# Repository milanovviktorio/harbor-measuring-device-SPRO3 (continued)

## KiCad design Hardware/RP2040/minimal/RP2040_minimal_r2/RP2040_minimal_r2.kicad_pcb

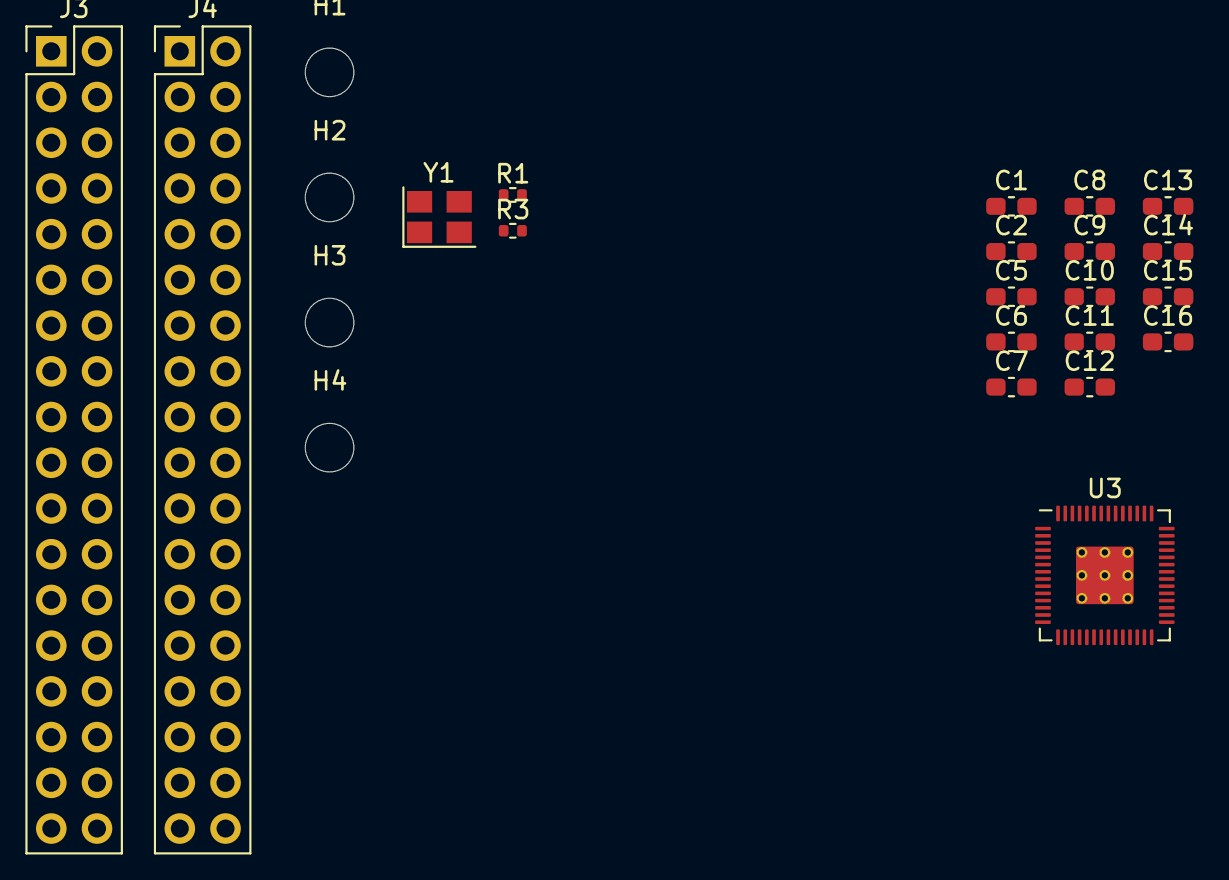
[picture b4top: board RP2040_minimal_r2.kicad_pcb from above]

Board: 2 copper layers, 24 parts (0 on the bottom side), 39 nets, no tracks yet.

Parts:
C1, C2: 27pF; C_0603_1608Metric_Pad1.08x0.95mm_HandSolder
C5, C6, C7, C9, C11, C12, C13, C14, C15, C16: 100n; C_0603_1608Metric_Pad1.08x0.95mm_HandSolder
C8, C10: 1u; C_0603_1608Metric_Pad1.08x0.95mm_HandSolder
H1, H2, H3, H4: MountingHole; MountingHole_2.7mm_M2.5
J3, J4: Conn_02x18_Odd_Even; PinHeader_2x18_P2.54mm_Vertical
R1: 1k; R_0402_1005Metric
R3: 10k; R_0402_1005Metric
U3: RP2040; RP2040-QFN-56
Y1: 12Mhz; Crystal_SMD_Abracon_ABM8G-4Pin_3.2x2.5mm

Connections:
+1V1: C6.1, C7.1, C8.1, U3.23 (DVDD), U3.45 (VREG_VOUT), U3.50 (DVDD)
+3V3: C5.1, C9.1, C10.1, C11.1, C12.1, C13.1, C14.1, C15.1, C16.1, J3.2, R3.1, U3.1 (IOVDD), U3.10 (IOVDD), U3.22 (IOVDD), U3.33 (IOVDD), U3.42 (IOVDD), U3.43 (ADC_AVDD), U3.44 (VREG_IN), U3.48 (USB_VDD), U3.49 (IOVDD)
/GPIO0: J3.4, U3.2 (GPIO0)
/GPIO1: J3.6, U3.3 (GPIO1)
/GPIO2: J3.8, U3.4 (GPIO2)
/GPIO3: J3.10, U3.5 (GPIO3)
/GPIO4: J3.12, U3.6 (GPIO4)
/GPIO5: J3.14, U3.7 (GPIO5)
/GPIO6: J3.16, U3.8 (GPIO6)
/GPIO7: J3.18, U3.9 (GPIO7)
/GPIO8: J3.20, U3.11 (GPIO8)
/GPIO9: J3.22, U3.12 (GPIO9)
/GPIO10: J3.24, U3.13 (GPIO10)
/GPIO11: J3.26, U3.14 (GPIO11)
/GPIO12: J3.28, U3.15 (GPIO12)
/GPIO13: J3.30, U3.16 (GPIO13)
/GPIO14: J3.32, U3.17 (GPIO14)
/GPIO15: J3.34, U3.18 (GPIO15)
/GPIO16: J4.27, U3.27 (GPIO16)
/GPIO17: J4.25, U3.28 (GPIO17)
/GPIO18: J4.23, U3.29 (GPIO18)
/GPIO19: J4.21, U3.30 (GPIO19)
/GPIO20: J4.19, U3.31 (GPIO20)
/GPIO21: J4.17, U3.32 (GPIO21)
/GPIO22: J4.15, U3.34 (GPIO22)
/GPIO23: J4.13, U3.35 (GPIO23)
/GPIO24: J4.11, U3.36 (GPIO24)
/GPIO25: J4.9, U3.37 (GPIO25)
/GPIO26_ADC0: J4.7, U3.38 (GPIO26_ADC0)
/GPIO27_ADC1: J4.5, U3.39 (GPIO27_ADC1)
/GPIO28_ADC2: J4.3, U3.40 (GPIO28_ADC2)
/GPIO29_ADC3: J4.1, U3.41 (GPIO29_ADC3)
/QSPI_SS: R1.1, R3.2, U3.56 (QSPI_SS)
/RUN: J4.29, U3.26 (RUN)
/SWCLK: J4.33, U3.24 (SWCLK)
/SWD: J4.31, U3.25 (SWD)
/XIN: C1.1, U3.20 (XIN), U3.21 (XOUT), Y1.1
GND: C1.2, C2.2, C5.2, C6.2, C7.2, C8.2, C9.2, C10.2, C11.2, C12.2, C13.2, C14.2, C15.2, C16.2, J3.1, J3.3, J3.5, J3.7, J3.9, J3.11, J3.13, J3.15, J3.17, J3.19, J3.21, J3.23, J3.25, J3.27, J3.29, J3.31, J3.33, J3.35, J3.36, J4.2, J4.4, J4.6, J4.8, J4.10, J4.12, J4.14, J4.16, J4.18, J4.20, J4.22, J4.24, J4.26, J4.28, J4.30, J4.32, J4.34, J4.35, J4.36, U3.19 (TESTEN), U3.57 (GND)
unnamed: C2.1, Y1.2

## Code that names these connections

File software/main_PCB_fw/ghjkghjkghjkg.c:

unsigned int motor_step;

void motor_commutate(int step);

void motor_pwm_setup();

void motor_pwm_startup();

void motor_pwm_state(uint pin, uint pin_comp, uint freq, float duty_cycle);

void motor_commutate(int step) {
    AS1_val=1;
    switch(step) {
        case 0:
            motor_pwm_state(ALS, AHS, 20000, AS1_val*0.8);
            motor_pwm_state(BLS, BHS, 20000, AS1_val*0.2);
            motor_pwm_state(CLS, CHS, 20000, AS1_val*0.0);
            break;
        case 1:
            motor_pwm_state(ALS, AHS, 20000, AS1_val*0.8);
            motor_pwm_state(BLS, BHS, 20000, AS1_val*0.0);
            motor_pwm_state(CLS, CHS, 20000, AS1_val*0.2);
            break;
        case 2:
            motor_pwm_state(ALS, AHS, 20000, AS1_val*0.2);
            motor_pwm_state(BLS, BHS, 20000, AS1_val*0.0);
            motor_pwm_state(CLS, CHS, 20000, AS1_val*0.2);
            break;
        case 3:
            motor_pwm_state(ALS, AHS, 20000, AS1_val*0.0);
            motor_pwm_state(BLS, BHS, 20000, AS1_val*0.2);
            motor_pwm_state(CLS, CHS, 20000, AS1_val*0.8);
            break;
        case 4:
            motor_pwm_state(ALS, AHS, 20000, AS1_val*0.0);
            motor_pwm_state(BLS, BHS, 20000, AS1_val*0.8);
            motor_pwm_state(CLS, CHS, 20000, AS1_val*0.2);
            break;
        case 5:
            motor_pwm_state(ALS, AHS, 20000, AS1_val*0.2);
            motor_pwm_state(BLS, BHS, 20000, AS1_val*0.8);
            motor_pwm_state(CLS, CHS, 20000, AS1_val*0.0);
            break;
    }
}

void motor_pwm_setup() {
  gpio_set_function(AHS, GPIO_FUNC_PWM);
  gpio_set_function(ALS, GPIO_FUNC_PWM);
  gpio_set_function(BHS, GPIO_FUNC_PWM);
  gpio_set_function(BLS, GPIO_FUNC_PWM);
  gpio_set_function(CHS, GPIO_FUNC_PWM);
  gpio_set_function(CLS, GPIO_FUNC_PWM);
}

void motor_pwm_startup() {
  motor_pwm_state(ALS, AHS, 20000, 0.8);
  motor_pwm_state(BLS, BHS, 20000, 0.2);
  motor_pwm_state(CLS, CHS, 20000, 0.0);
  delay(100);
  motor_pwm_state(ALS, AHS, 20000, 0.8);
  motor_pwm_state(BLS, BHS, 20000, 0.0);
  motor_pwm_state(CLS, CHS, 20000, 0.2);
  delay(100);
  motor_pwm_state(ALS, AHS, 20000, 0.2);
  motor_pwm_state(BLS, BHS, 20000, 0.0);
  motor_pwm_state(CLS, CHS, 20000, 0.2);
  delay(100);
  motor_pwm_state(ALS, AHS, 20000, 0.0);
  motor_pwm_state(BLS, BHS, 20000, 0.2);
  motor_pwm_state(CLS, CHS, 20000, 0.8);
  delay(100);
  motor_pwm_state(ALS, AHS, 20000, 0.0);
  motor_pwm_state(BLS, BHS, 20000, 0.8);
  motor_pwm_state(CLS, CHS, 20000, 0.2);
  delay(100);
  motor_pwm_state(ALS, AHS, 20000, 0.2);
  motor_pwm_state(BLS, BHS, 20000, 0.8);
  motor_pwm_state(CLS, CHS, 20000, 0.0);
  motor_step=5;
  delay(100);
  Serial.println("Tried to start motor");
  attachInterrupt(digitalPinToInterrupt(BEMF), BEMF_call, RISING);
  Serial.println("Hand-off to interrupt");
}

void BEMF_call() {
  delayMicroseconds(8);
  motor_step++;
  if(motor_step>5 || motor_step<0)
    motor_step=0;
  motor_commutate(motor_step);
}

void motor_pwm_state(uint pin, uint pin_comp, uint freq, float duty_cycle) {
  uint slice_num = pwm_gpio_to_slice_num(pin);
  uint channel = pwm_gpio_to_channel(pin);
  uint channel2 = pwm_gpio_to_channel(pin_comp);
  
  uint32_t clock = clock_get_hz(clk_sys); // system clock
  uint32_t divider = 1;                   // integer divider
  uint32_t wrap = clock / (divider * freq) - 1;
  
  pwm_set_clkdiv(slice_num, divider);
  pwm_set_wrap(slice_num, wrap);

  pwm_set_output_polarity(slice_num, true, false);

  if (duty_cycle < 0.0f) duty_cycle = 0.0f;
  if (duty_cycle > 1.0f) duty_cycle = 1.0f;

  uint32_t level = (uint32_t)(duty_cycle * wrap);

  pwm_set_chan_level(slice_num, channel, level);
  pwm_set_chan_level(slice_num, channel2, level);

  pwm_set_enabled(slice_num, true);
}

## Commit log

2025-10-13 created basic folder structure
2025-10-13 basic folder structure vol2
2025-10-13 platform example for pico under arduino
2025-10-14 Added documents folder with comparison for 'Micropython vs C++'
2025-10-19 Add files via upload
    a added bare minimum. NOTE it's will be noisy as fuck make sure to put caps as close to mcu as possible avoid cables use net zones;))
2025-10-21 Started developing the Main PCB
2025-10-22 Added Buck and Boost converter as well as a basic RP2040 circuit
2025-10-22 Fixed stupid things on the boost converter
2025-10-24 Made the simulations for the Main PCB
2025-10-26 Create ESC_BMS
2025-10-26 Trustworthy version of the MAIN PCB schematic
2025-10-26 fixed folder struct
2025-10-26 Updated to match connectors from ESC/BMS board, other corrections
2025-10-26 RF test on pico sdk
2025-10-28 Added some footprints
2025-10-28 Updated SPROJ3EE_ESC_BMS.kicad_sch to include more caps
2025-10-28 Updated 1.ECS.kicad_sch to put more caps and fix some nets
2025-10-28 Updated 2.BMS.kicad_sch to add bulk capacitance
2025-10-29 initial BMS work
2025-10-30 Modifications to the MainPCB
2025-10-30 Updated sonar.kicad_sch with a new sonar connector
2025-10-30 Updated Main_PCB.kicad_sch with servo connector
2025-10-30 A finished version of the Main PCB schematic
2025-10-31 Added footprints to all components
2025-10-31 some more BMS work + fixed RP2040 XIN/XOUT shortage
2025-11-01 Finished the schematic of the MainPCB
2025-11-01 start adding RC PCB bits (not finished at all)
2025-11-01 cleanup
2025-11-02 Some footprint positioning
2025-11-02 RC thing schematic 70% done
2025-11-04 BMS almost full
2025-11-04 more rc stuff (trust)
2025-11-05 more BMS
2025-11-05 Placement almost complete on MainPCB
2025-11-06 Probably a final version of the MAIN PCB component placement
2025-11-06 fixed voltage divider for controller batt status
2025-11-06 Made the power supply planes and traces
2025-11-07 Work on the PCB
2025-11-07 Finished the routing - V1
2025-11-07 Updated the PCB with new USB-C
2025-11-08 Simulations for BMS start and footprints
2025-11-09 Footprints + final schematic _/\_
2025-11-10 footprints almost done and LEDs for charger fixed
2025-11-10 update pin layout to make PCB easier
2025-11-11 more stuff related to RF pinout on RC controller
2025-11-11 G is too lazy to upload his schematic
2025-11-11 more pinout changes :upside_down_smile:
2025-11-11 ESC/BMS fully ready for PCB
2025-11-11 V1.1 of the MainPCB
2025-11-12 Should be finished version of MainPCB - v2
2025-11-12 Finished MainPCB v3
2025-11-12 Small adjustment to top silkscreen on MainPCB
2025-11-12 ESC/BMS PCB started
2025-11-13 PCB component placement init
2025-11-13 the G-ening
2025-11-13 cleanup 2
2025-11-13 current state of Rc
2025-11-13 ESC BMS component placement close to done
2025-11-13 RC thing PCB 95% trustworthy (six seven)
2025-11-14 ESC done
2025-11-15 new RC PCB updates
2025-11-15 G will be touched tonight
2025-11-16 Changed the IMU sensor on the MainPCB
2025-11-16 Minor adjustments to MainPCB
2025-11-16 ESC/BMS board done _/\_ (without silkscreen)
2025-11-17 ESC/BMS board done _/\_ (with full silkscreen) - just 12 warnings
2025-11-17 Light rework of ESC/BMS layout
2025-11-17 Reviewed .sch
2025-11-17 trustworthy(?) RC PCB
2025-11-17 ESC/BMS board done fully
2025-11-17 ESC/BMS board done fully fully
2025-11-17 ESC/BMS board done fully fully fully
2025-11-18 Reverted to the previous IMU
2025-11-18 fixing DRC errors on RC
2025-11-18 Small adjustments
2025-11-18 Stitching GND, silkscreen thickness, increased thermal distribution of charger IC
2025-11-18 Footprint updated
2025-11-18 little pin change in software
2025-11-18 vanity
2025-11-18 MainPCB Final version
2025-11-18 ESC/BMS board with SDU logo (slick)
2025-11-18 Final touches
2025-12-03 pico project start for main pcb
2025-12-04 started implementing motor driver code
2025-12-04 more motor stuff (now arduino'd)
2025-12-06 oled example software made
2025-12-07 procrastination final boss
2025-12-07 the radio kinda works ig
2025-12-09 stuff
2025-12-10 IMU code fully working
2025-12-10 IMU code small pin adjustment and Servo motor swinging code
2025-12-10 Made a skeleton for the Main PCB code
2025-12-10 BLDC code that actually works as it should
2025-12-10 more code n shit
2025-12-12 more stuff
2025-12-14 some sonar functions + some basics for RF (main doesn't compile rn)
2025-12-15 main PCB work. TUSS code might work (doubtful)
2025-12-16 RF transmit/receive. Works until whining happens. Fixable. Trust.
2025-12-17 Some sonar code. Unreliable in air, idk bout water
2025-12-20 Minor adjustments to BMS schematic - beautifying
2025-12-22 Beautifying the Master Controller
2026-01-22 more stuff (ESC exploded)
2026-01-25 fixed vprot and gnd comp error
2026-01-25 fixed drain and source error bms
2026-01-26 stutf
2026-01-27 final plate of spaghetti
    kill me
